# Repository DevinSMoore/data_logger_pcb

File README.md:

# data_logger_pcb
Data Acquisition data logger PCB KiCad files (kiCad 6.0)

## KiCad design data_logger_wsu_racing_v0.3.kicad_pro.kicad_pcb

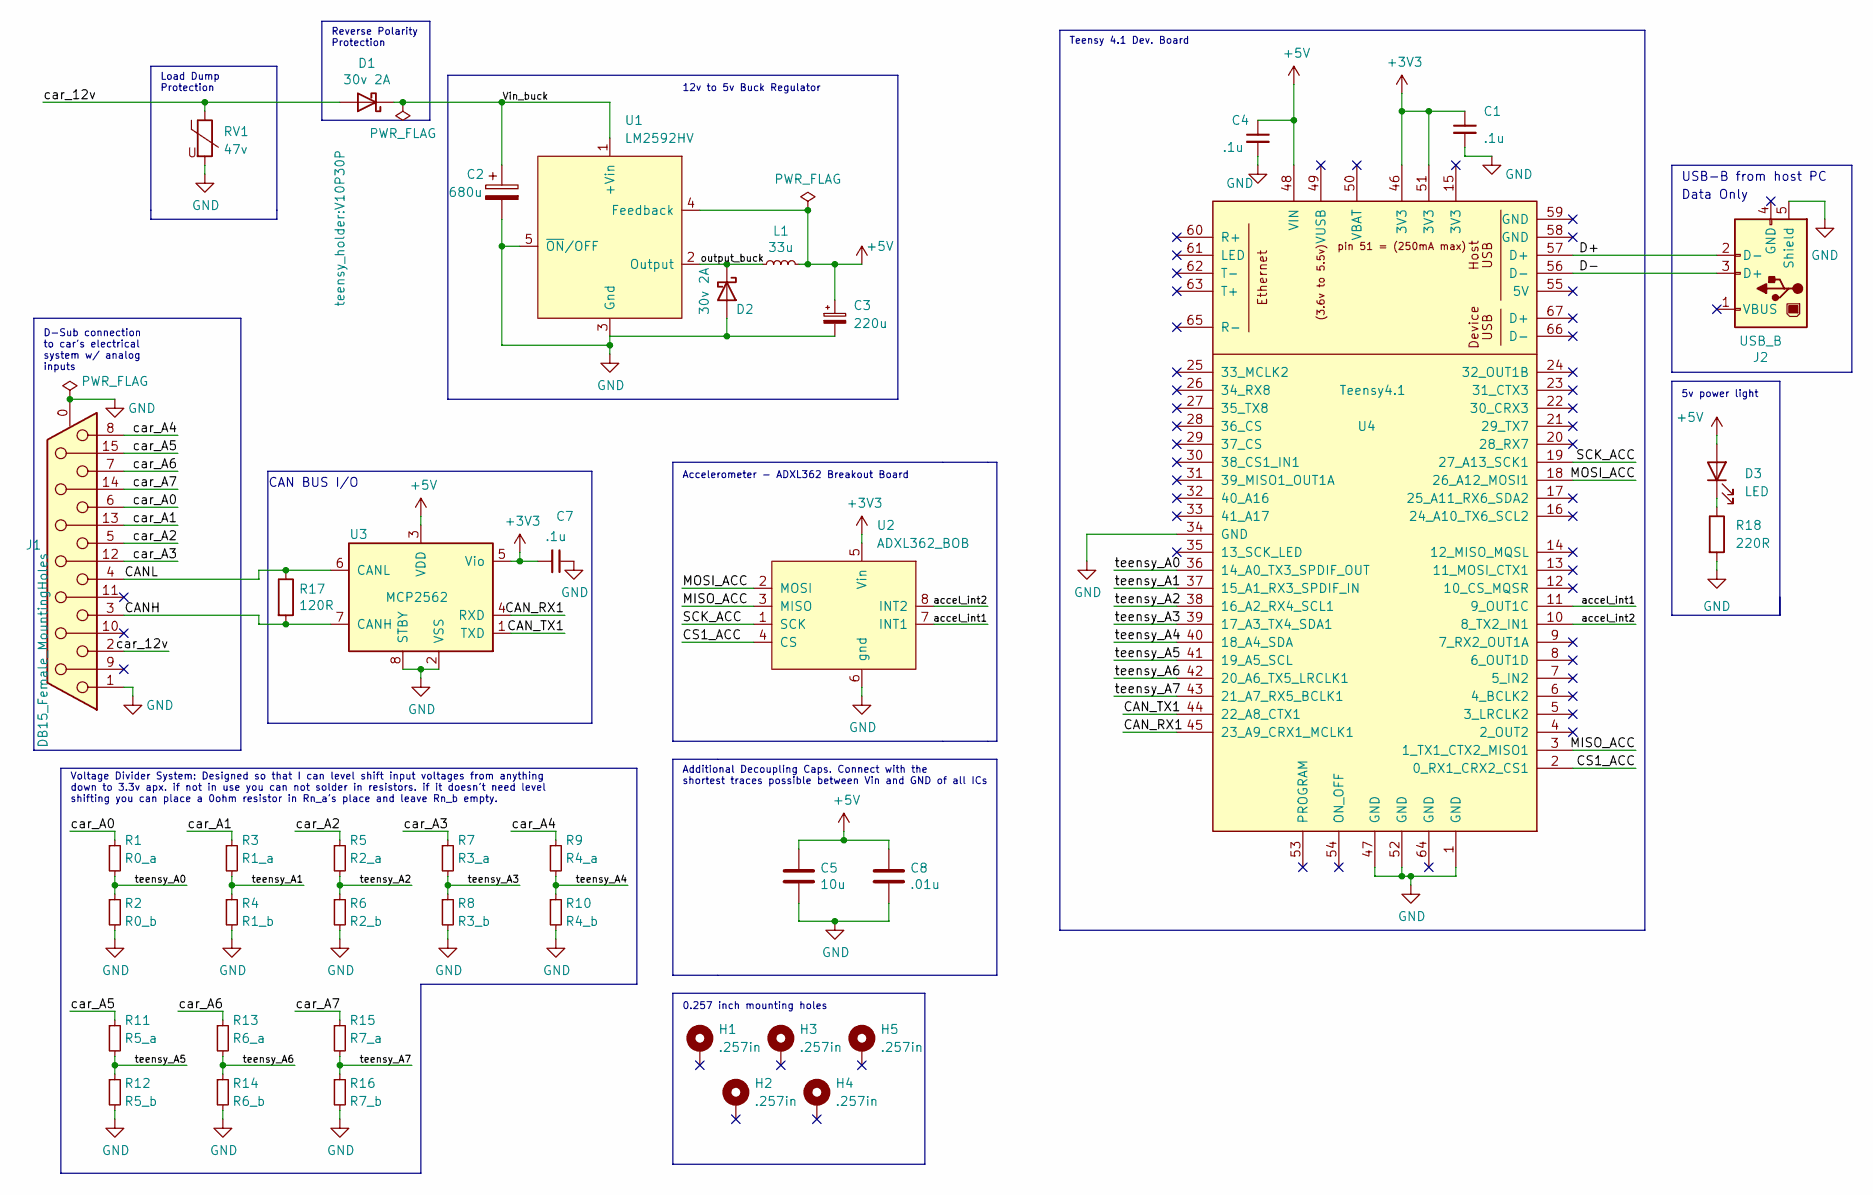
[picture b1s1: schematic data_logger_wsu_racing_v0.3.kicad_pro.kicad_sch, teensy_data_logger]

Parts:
C1, C4, C7: .1u; C_Disc_D5.1mm_W3.2mm_P5.00mm
C2: 680u; CP_Radial_D10.0mm_P5.00mm
C3: 220u; CP_Axial_L30.0mm_D10.0mm_P35.00mm_Horizontal
C5: 10u; C_Disc_D5.0mm_W2.5mm_P2.50mm
C8: .01u; C_Disc_D3.8mm_W2.6mm_P2.50mm
D1, D2: 30v 2A; D_DO-41_SOD81_P7.62mm_Horizontal
D3: LED; LED_D3.0mm
H1, H2, H3, H4, H5: .257in; MountingHole_0.257_in_Pad_Via
J1: DB15_Female_MountingHoles; DSUB-15_Female_Horizontal_P2.77x2.84mm_EdgePinOffset7.70mm_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
J2: USB_B; USB_B_OST_USB-B1HSxx_Horizontal
L1: 33u; L_Radial_D9.5mm_P5.00mm_Fastron_07HVP
R1: R0_a; R_Axial_DIN0207_L6.3mm_D2.5mm_P10.16mm_Horizontal
R2: R0_b; R_Axial_DIN0207_L6.3mm_D2.5mm_P10.16mm_Horizontal
R3: R1_a; R_Axial_DIN0207_L6.3mm_D2.5mm_P10.16mm_Horizontal
R4: R1_b; R_Axial_DIN0207_L6.3mm_D2.5mm_P10.16mm_Horizontal
R5: R2_a; R_Axial_DIN0207_L6.3mm_D2.5mm_P10.16mm_Horizontal
R6: R2_b; R_Axial_DIN0207_L6.3mm_D2.5mm_P10.16mm_Horizontal
R7: R3_a; R_Axial_DIN0207_L6.3mm_D2.5mm_P10.16mm_Horizontal
R8: R3_b; R_Axial_DIN0207_L6.3mm_D2.5mm_P10.16mm_Horizontal
R9: R4_a; R_Axial_DIN0207_L6.3mm_D2.5mm_P10.16mm_Horizontal
R10: R4_b; R_Axial_DIN0207_L6.3mm_D2.5mm_P10.16mm_Horizontal
R11: R5_a; R_Axial_DIN0207_L6.3mm_D2.5mm_P10.16mm_Horizontal
R12: R5_b; R_Axial_DIN0207_L6.3mm_D2.5mm_P10.16mm_Horizontal
R13: R6_a; R_Axial_DIN0207_L6.3mm_D2.5mm_P10.16mm_Horizontal
R14: R6_b; R_Axial_DIN0207_L6.3mm_D2.5mm_P10.16mm_Horizontal
R15: R7_a; R_Axial_DIN0207_L6.3mm_D2.5mm_P10.16mm_Horizontal
R16: R7_b; R_Axial_DIN0207_L6.3mm_D2.5mm_P10.16mm_Horizontal
R17: 120R; R_Axial_DIN0207_L6.3mm_D2.5mm_P10.16mm_Horizontal
R18: 220R; R_Axial_DIN0207_L6.3mm_D2.5mm_P10.16mm_Horizontal
RV1: 47v; V10P30P
U1: LM2592HV; TO-220-5_P3.4x3.7mm_StaggerOdd_Lead3.8mm_Vertical
U2: ADXL362_BOB; adxl362BOB_footprint
U3: MCP2562; DIP-8_W7.62mm
U4: Teensy4.1; Teensy41

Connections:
+3V3: C1.1, C7.2, U2.5 (Vin), U3.5 (Vio), U4.46 (3V3), U4.51 (3V3)
+5V: C3.1, C4.1, C5.1, C8.1, D3.2 (A), L1.2, U1.4 (Feedback), U3.3 (VDD), U4.48 (VIN)
/CANH: J1.3, R17.2, U3.7 (CANH)
/CANL: J1.4, R17.1, U3.6 (CANL)
/CAN_RX1: U3.4 (RXD), U4.45 (23_A9_CRX1_MCLK1)
/CAN_TX1: U3.1 (TXD), U4.44 (22_A8_CTX1)
/CS1_ACC: U2.4 (CS), U4.2 (0_RX1_CRX2_CS1)
/D+: J2.2 (D-), U4.57 (D+)
/D-: J2.3 (D+), U4.56 (D-)
/MISO_ACC: U2.3 (MISO), U4.3 (1_TX1_CTX2_MISO1)
/MOSI_ACC: U2.2 (MOSI), U4.18 (26_A12_MOSI1)
/SCK_ACC: U2.1 (SCK), U4.19 (27_A13_SCK1)
/Vin_buck: C2.1, D1.1 (K), U1.1 (+Vin)
/accel_int1: U2.7 (INT1), U4.11 (9_OUT1C)
/accel_int2: U2.8 (INT2), U4.10 (8_TX2_IN1)
/car_12v: D1.2 (A), J1.2, RV1.1
/car_A0: J1.6, R1.1
/car_A1: J1.13, R3.1
/car_A2: J1.5, R5.1
/car_A3: J1.12, R7.1
/car_A4: J1.8, R9.1
/car_A5: J1.15, R11.1
/car_A6: J1.7, R13.1
/car_A7: J1.14, R15.1
/output_buck: D2.1 (K), L1.1, U1.2 (Output)
/teensy_A0: R1.2, R2.1, U4.36 (14_A0_TX3_SPDIF_OUT)
/teensy_A1: R3.2, R4.1, U4.37 (15_A1_RX3_SPDIF_IN)
/teensy_A2: R5.2, R6.1, U4.38 (16_A2_RX4_SCL1)
/teensy_A3: R7.2, R8.1, U4.39 (17_A3_TX4_SDA1)
/teensy_A4: R9.2, R10.1, U4.40 (18_A4_SDA)
/teensy_A5: R11.2, R12.1, U4.41 (19_A5_SCL)
/teensy_A6: R13.2, R14.1, U4.42 (20_A6_TX5_LRCLK1)
/teensy_A7: R15.2, R16.1, U4.43 (21_A7_RX5_BCLK1)
GND: C1.2, C2.2, C3.2, C4.2, C5.2, C7.1, C8.2, D2.2 (A), J1.0 (PAD), J1.1, J2.5 (Shield), R2.2, R4.2, R6.2, R8.2, R10.2, R12.2, R14.2, R16.2, R18.2, RV1.2, U1.3 (Gnd), U1.5 (~ON/OFF), U2.6 (gnd), U3.2 (VSS), U3.8 (STBY), U4.1 (GND), U4.34 (GND), U4.47 (GND), U4.52 (GND)
unnamed: D3.1 (K), R18.1

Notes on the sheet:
Accelerometer - ADXL362 Breakout Board
Additional Decoupling Caps. Connect with the shortest traces possible between Vin and GND of all ICs
CAN BUS I/O
Reverse Polarity Protection
5v power light
0.257 inch mounting holes
Teensy 4.1 Dev. Board
USB-B from host PC
12v to 5v Buck Regulator
D-Sub connection to car's electrical system w/ analog inputs
Voltage Divider System: Designed so that I can level shift input voltages from anything down to 3.3v apx. if not in use you can not solder in resistors. if it doesn't need level shifting you can place a 0ohm resistor in Rn_a's place and leave Rn_b empty.
Data Only
Load Dump Protection

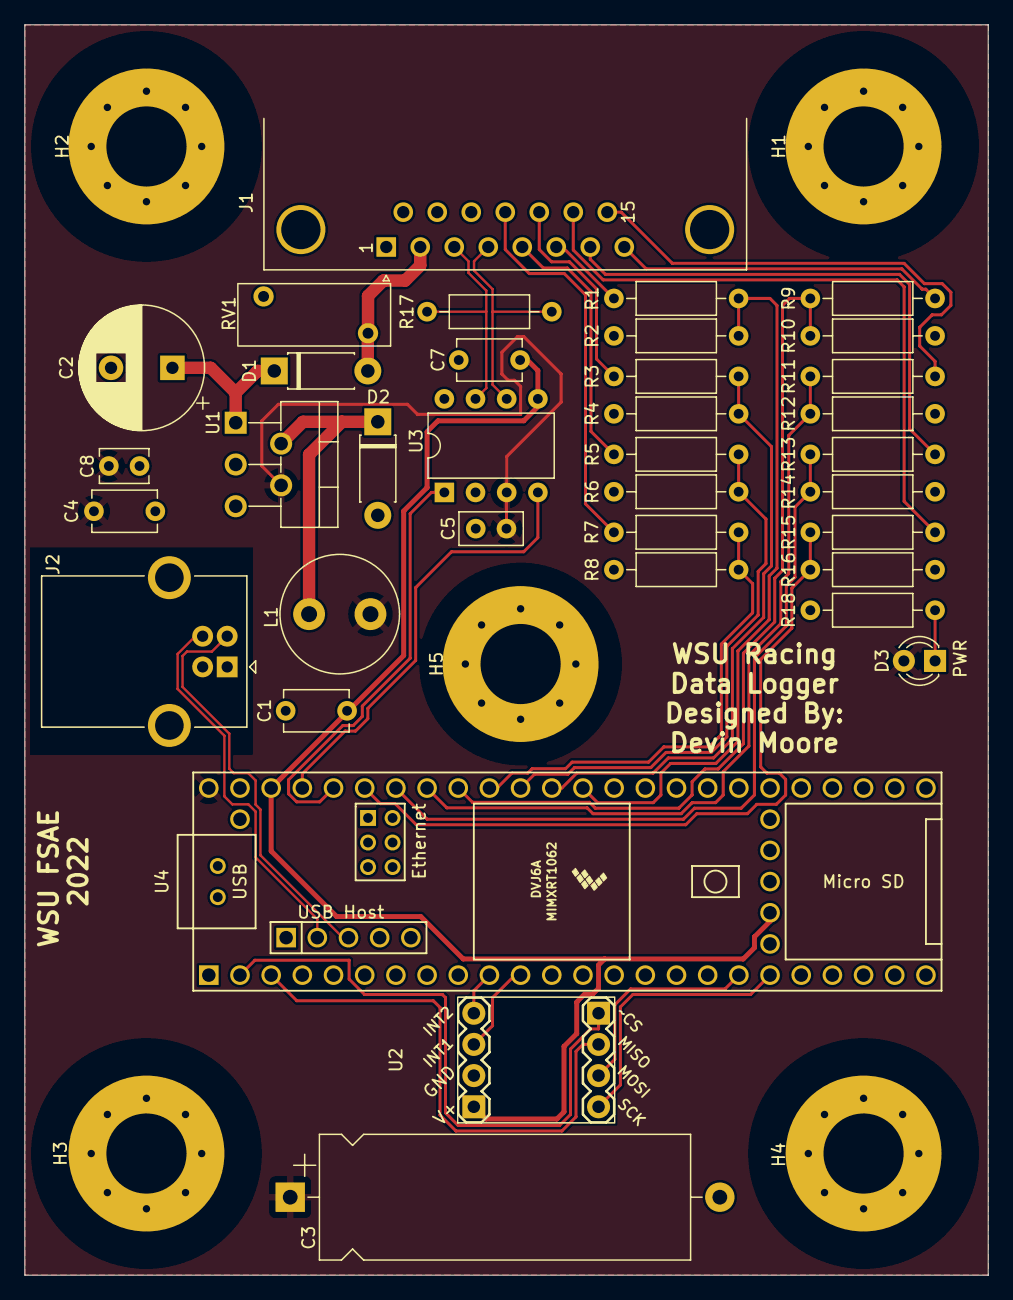
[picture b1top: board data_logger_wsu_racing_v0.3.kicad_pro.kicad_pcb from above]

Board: 2 copper layers, 78.5 x 101.9 mm, 41 parts (0 on the bottom side), 35 nets.

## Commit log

2022-04-01 Add files via upload
    Initial commit of data logger pcb files. version 0.3 has yet to be verified. Once I receive it I will go through that process.
2022-06-12 Fixed D+ and D- lines on the USB host bus.
